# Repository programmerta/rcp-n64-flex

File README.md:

# N64 Cart Relocation Flex for N64HH
A flex cable for easy relocation of the N64 cartridge slot for an N64HH build. Requires KiCad 8.99 (the nightly build) to view.

## Ordering Guide
> [!IMPORTANT]
> When ordering through a site such as JLCPCB, make sure you select an "FR4" stiffener at a 1.0mm thickness. This stiffener adds rigidity to the mounting points on the cart itself, so I wouldn't skip this to cut costs. You could try ordering with Polyimide to see if it's cheaper.

Under "PCB Remark", add the following message:

> [!NOTE]
> Please apply the stiffener to the bottom of the flex as shown in the stiffener.gbr file. The circles on that layer should be holes in the stiffener as well.

It is very important that the stiffener is on the BOTTOM of the flex, and not the top. The silkscreen on the flex mentions this as well. The stiffener.gbr is just the renamed user.drawing layer that specifies the outline of the stiffener.

## Special Thanks
I want to give a special thanks to the following individuals who helped me greatly with making this flex!

- [YveltalGriffin](https://twitter.com/YveltalGriffin) for feedback on the flex design and all his help with redesigning the board to greatly improve on my initial terrible attempt!
- [CrazyGadget](https://twitter.com/crazygadgetmods) for providing me with the inspiration and the initial RCP breakout files to help get me started on this project!

## License

Permissively released under the Solderpad Hardware License v2.1

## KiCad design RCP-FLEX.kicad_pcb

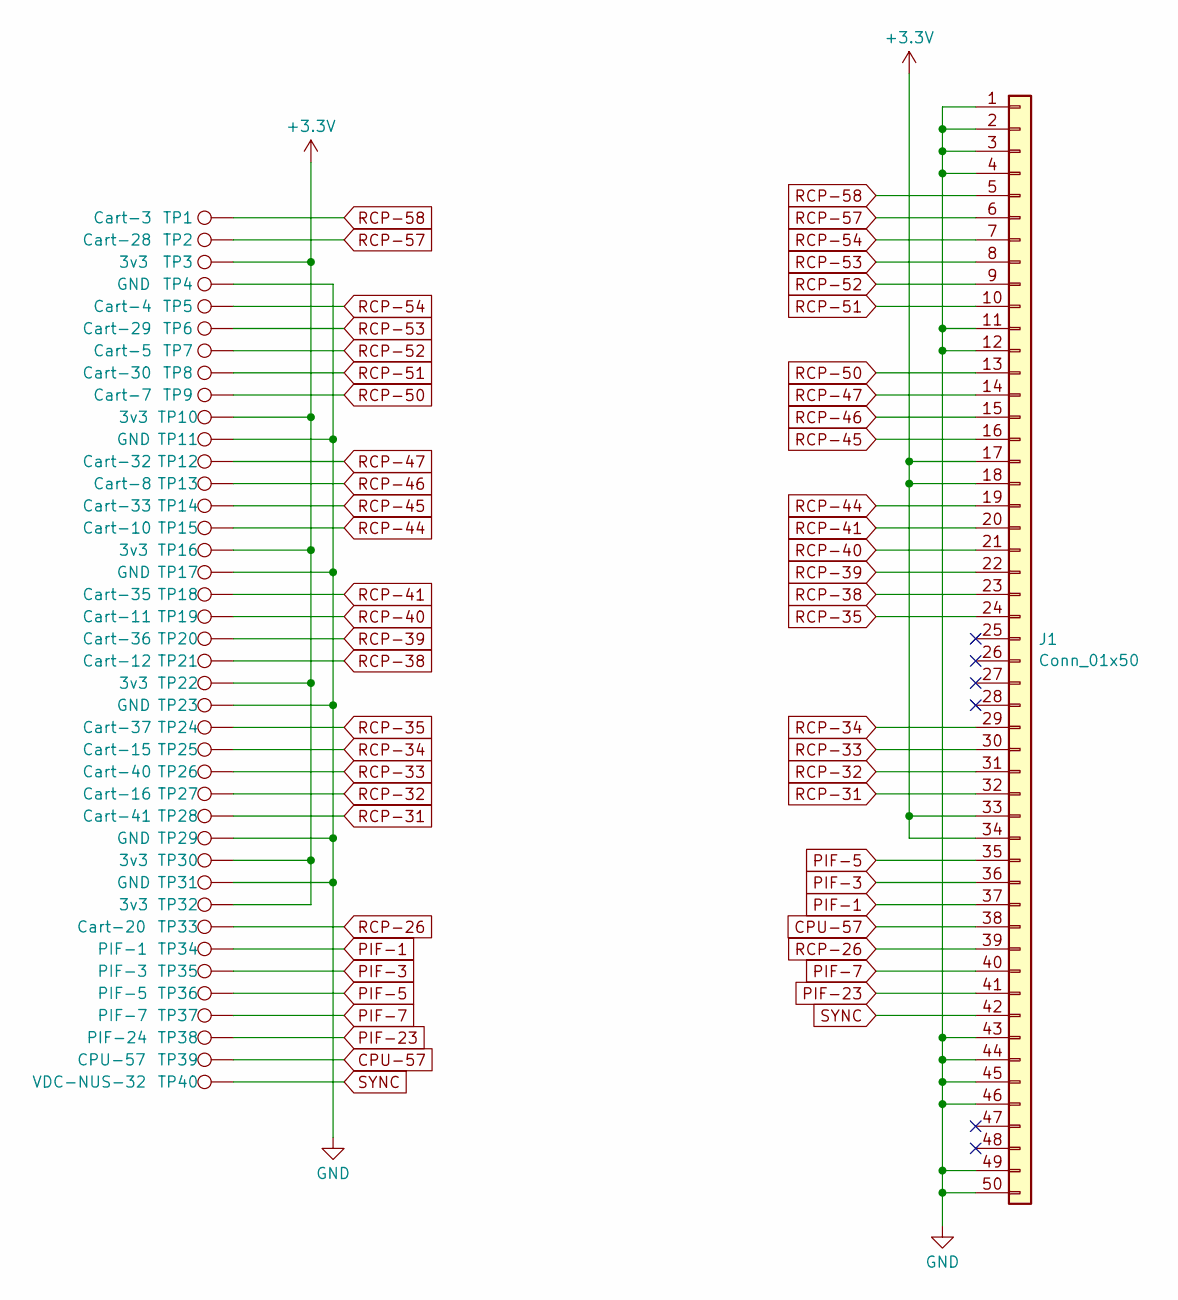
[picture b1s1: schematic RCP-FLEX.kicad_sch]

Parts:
J1: Conn_01x50; 2x25_P2.5mm
TP1: Cart-3; TestPoint_RCP-NUS
TP2: Cart-28; TestPoint_RCP-NUS
TP3, TP10, TP16, TP22, TP30, TP32: 3v3; TestPoint_RCP-NUS
TP4, TP11, TP17, TP23, TP29, TP31: GND; TestPoint_RCP-NUS
TP5: Cart-4; TestPoint_RCP-NUS
TP6: Cart-29; TestPoint_RCP-NUS
TP7: Cart-5; TestPoint_RCP-NUS
TP8: Cart-30; TestPoint_RCP-NUS
TP9: Cart-7; TestPoint_RCP-NUS
TP12: Cart-32; TestPoint_RCP-NUS
TP13: Cart-8; TestPoint_RCP-NUS
TP14: Cart-33; TestPoint_RCP-NUS
TP15: Cart-10; TestPoint_RCP-NUS
TP18: Cart-35; TestPoint_RCP-NUS
TP19: Cart-11; TestPoint_RCP-NUS
TP20: Cart-36; TestPoint_RCP-NUS
TP21: Cart-12; TestPoint_RCP-NUS
TP24: Cart-37; TestPoint_RCP-NUS
TP25: Cart-15; TestPoint_RCP-NUS
TP26: Cart-40; TestPoint_RCP-NUS
TP27: Cart-16; TestPoint_RCP-NUS
TP28: Cart-41; TestPoint_RCP-NUS
TP33: Cart-20; TestPoint_RCP-NUS
TP34: PIF-1; TestPoint_Pad_D1.0mm
TP35: PIF-3; TestPoint_Pad_D1.0mm
TP36: PIF-5; TestPoint_Pad_D1.0mm
TP37: PIF-7; TestPoint_Pad_D1.0mm
TP38: PIF-24; TestPoint_Pad_D1.0mm
TP39: CPU-57; TestPoint_Pad_D1.0mm
TP40: VDC-NUS-32; TestPoint_Pad_D1.0mm

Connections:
+3.3V: J1.17, J1.18, J1.33, J1.34, TP3.1, TP10.1, TP16.1, TP22.1, TP30.1, TP32.1
CPU-57: J1.38, TP39.1
GND: J1.1, J1.2, J1.3, J1.4, J1.11, J1.12, J1.43, J1.44, J1.45, J1.46, J1.49, J1.50, TP4.1, TP11.1, TP17.1, TP23.1, TP29.1, TP31.1
PIF-1: J1.37, TP34.1
PIF-3: J1.36, TP35.1
PIF-5: J1.35, TP36.1
PIF-7: J1.40, TP37.1
PIF-23: J1.41, TP38.1
RCP-26: J1.39, TP33.1
RCP-31: J1.32, TP28.1
RCP-32: J1.31, TP27.1
RCP-33: J1.30, TP26.1
RCP-34: J1.29, TP25.1
RCP-35: J1.24, TP24.1
RCP-38: J1.23, TP21.1
RCP-39: J1.22, TP20.1
RCP-40: J1.21, TP19.1
RCP-41: J1.20, TP18.1
RCP-44: J1.19, TP15.1
RCP-45: J1.16, TP14.1
RCP-46: J1.15, TP13.1
RCP-47: J1.14, TP12.1
RCP-50: J1.13, TP9.1
RCP-51: J1.10, TP8.1
RCP-52: J1.9, TP7.1
RCP-53: J1.8, TP6.1
RCP-54: J1.7, TP5.1
RCP-57: J1.6, TP2.1
RCP-58: J1.5, TP1.1
SYNC: J1.42, TP40.1

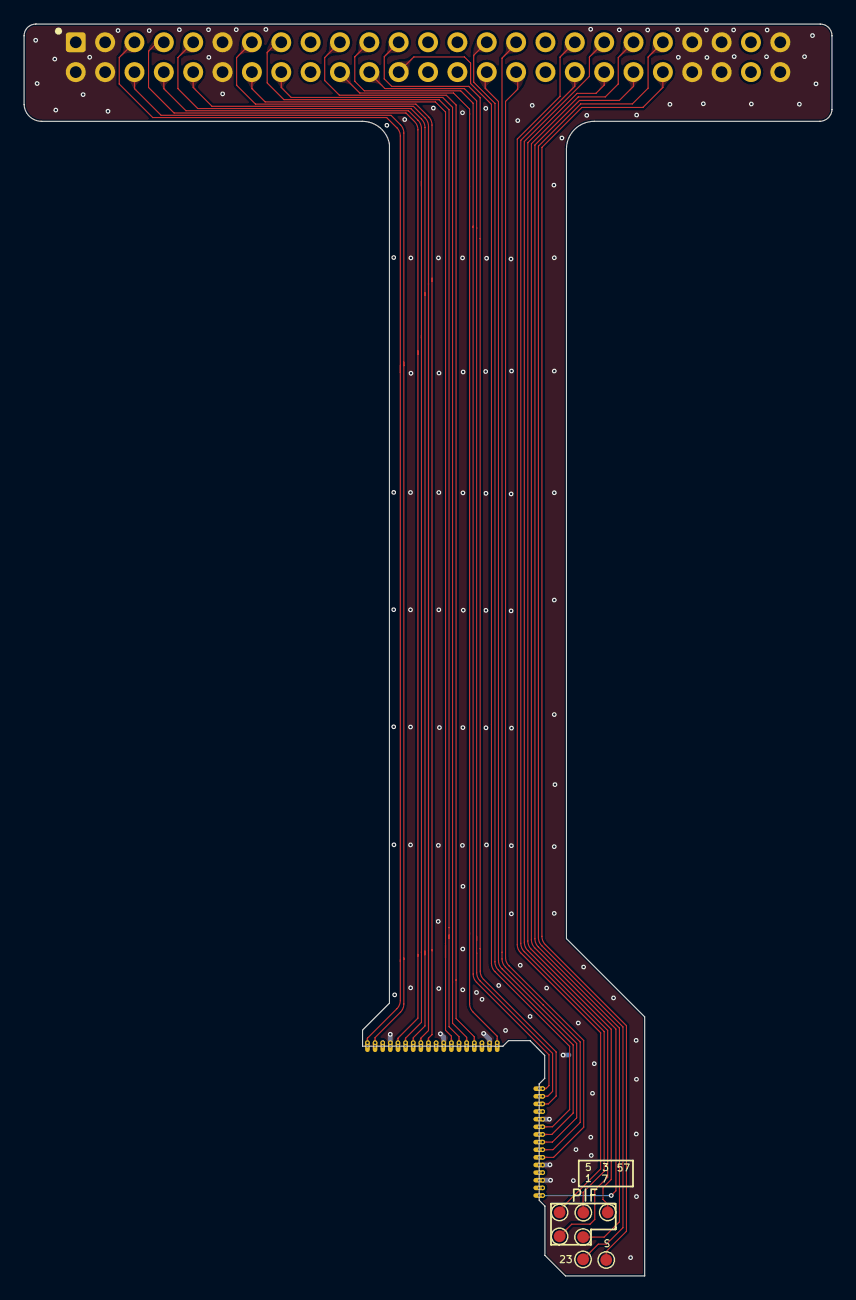
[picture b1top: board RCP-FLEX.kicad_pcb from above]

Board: 4 copper layers, 68.8 x 106.6 mm, 41 parts (1 on the bottom side), 30 nets.

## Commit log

2024-05-04 init
2024-05-04 cleanup
2024-05-04 updating readme
2024-05-04 readme updates
2024-05-04 readme update
